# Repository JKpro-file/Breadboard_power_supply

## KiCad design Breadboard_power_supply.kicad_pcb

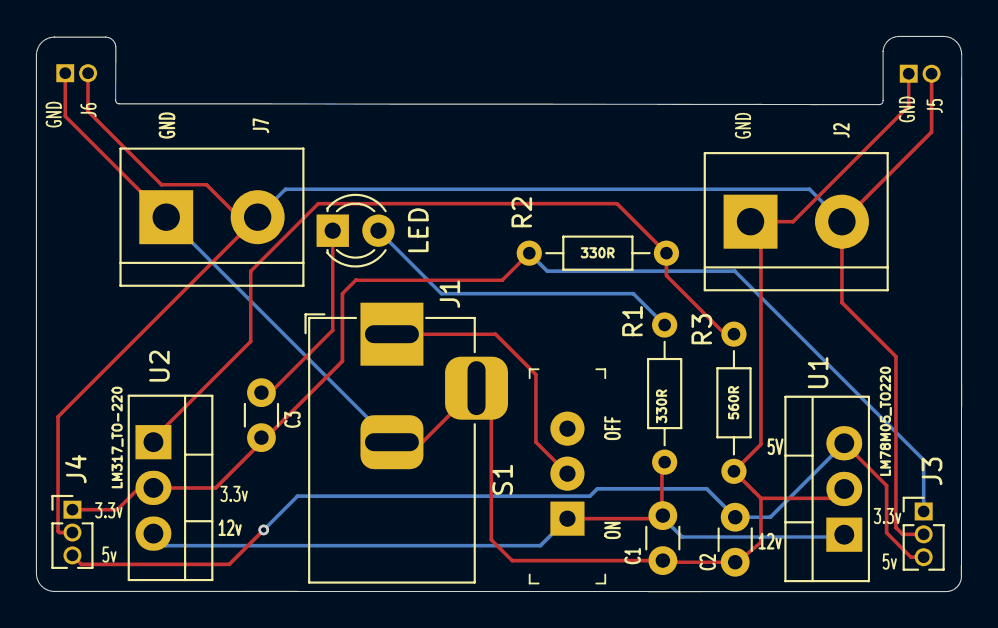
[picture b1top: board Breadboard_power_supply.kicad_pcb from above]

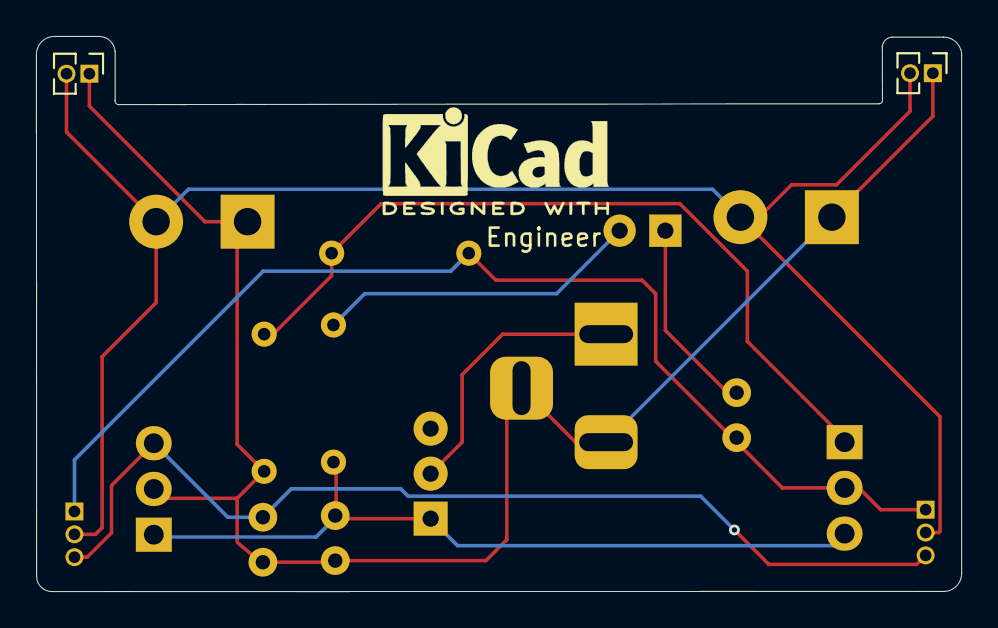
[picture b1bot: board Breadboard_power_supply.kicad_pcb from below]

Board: 2 copper layers, 51.4 x 30.8 mm, 17 parts (2 on the bottom side), 9 nets.

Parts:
C1, C2, C3: C; C_Disc_D3.0mm_W1.6mm_P2.50mm
D1: LED; LED_D3.0mm
J1: Barrel_Jack_Switch; BarrelJack_Horizontal
J2, J7: Screw_Terminal_01x02; TerminalBlock_bornier-2_P5.08mm
J3, J4: Conn_01x03_Pin; PinHeader_1x03_P1.27mm_Vertical
J5, J6: Conn_01x02_Pin; PinHeader_1x02_P1.27mm_Vertical
R1, R3: 560R; R_Axial_DIN0204_L3.6mm_D1.6mm_P7.62mm_Horizontal
R2: 330R; R_Axial_DIN0204_L3.6mm_D1.6mm_P7.62mm_Horizontal
S1: EG1218; Switch_Slide_11.6x4mm_EG1218
U1: LM78M05_TO220; TO-220-3_Vertical
U2: LM317_TO-220; TO-220-3_Vertical

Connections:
/3.3V: C3.1, J3.1, J4.1, R2.1, U2.2 (VO)
/5V: C2.1, J3.3, J4.3, U1.3 (VO)
/12V: C1.1, R1.1, S1.1, U1.1 (VI), U2.3 (VI)
/PWR_input: J1.1, S1.2
/PWR_output: J2.2, J3.2, J4.2, J5.2, J6.2, J7.2
GND: C1.2, C2.2, J1.2, J1.3, J2.1, J5.1, J6.1, J7.1, R3.2, U1.2 (GND)
unnamed: D1.2 (A), R1.2
unnamed: C3.2, D1.1 (K)
unnamed: R2.2, R3.1, U2.1 (ADJ)

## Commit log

2025-05-15 Filled the GND Copper zone in front & Back layers
2025-05-15 Removed Breadboard_power_supply-board folder from tracking.
2025-05-15 Ignored the gitignore file
2025-05-15 No changes
